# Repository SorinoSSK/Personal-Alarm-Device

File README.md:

# Introduction
This repository serves as a record and learning journey on hardware used for my capstone project. The objective of the project is to implement a small, affordable and unrestrictive IoT deviced that enables individuals to call for help in an emergency.

## PCB_Design_GSM_GPS
With the failure to find an appropriate module that carries both the functionality of GPS and GSM, I have decided to design a customised module using [SIM868](https://www.alibaba.com/product-detail/SIM868-Signal-Circuits-GSM-GPS-GNSS_1600272320629.html). SIM868 enables both GSM and GPS communication that is inline with the frequency band used in Singapore, however SIM868 is built for 2G communication and 2G communication is no longer used in Singapore. 

***Update: SIM868 is mostly no longer in production.***\
***SIM868 could not detect 3G or 4G network***

## Schematic_1
Upon searching for SIM868, I stumble across the module A9G and thus drew the schematic to be used for feasibility testing of our idea. A9G also uses GPRS protocol which still runs mostly on a [2G network](https://tinyurl.com/mwhuy22j). 

***Update: A9G could not detect 3G or 4G network***

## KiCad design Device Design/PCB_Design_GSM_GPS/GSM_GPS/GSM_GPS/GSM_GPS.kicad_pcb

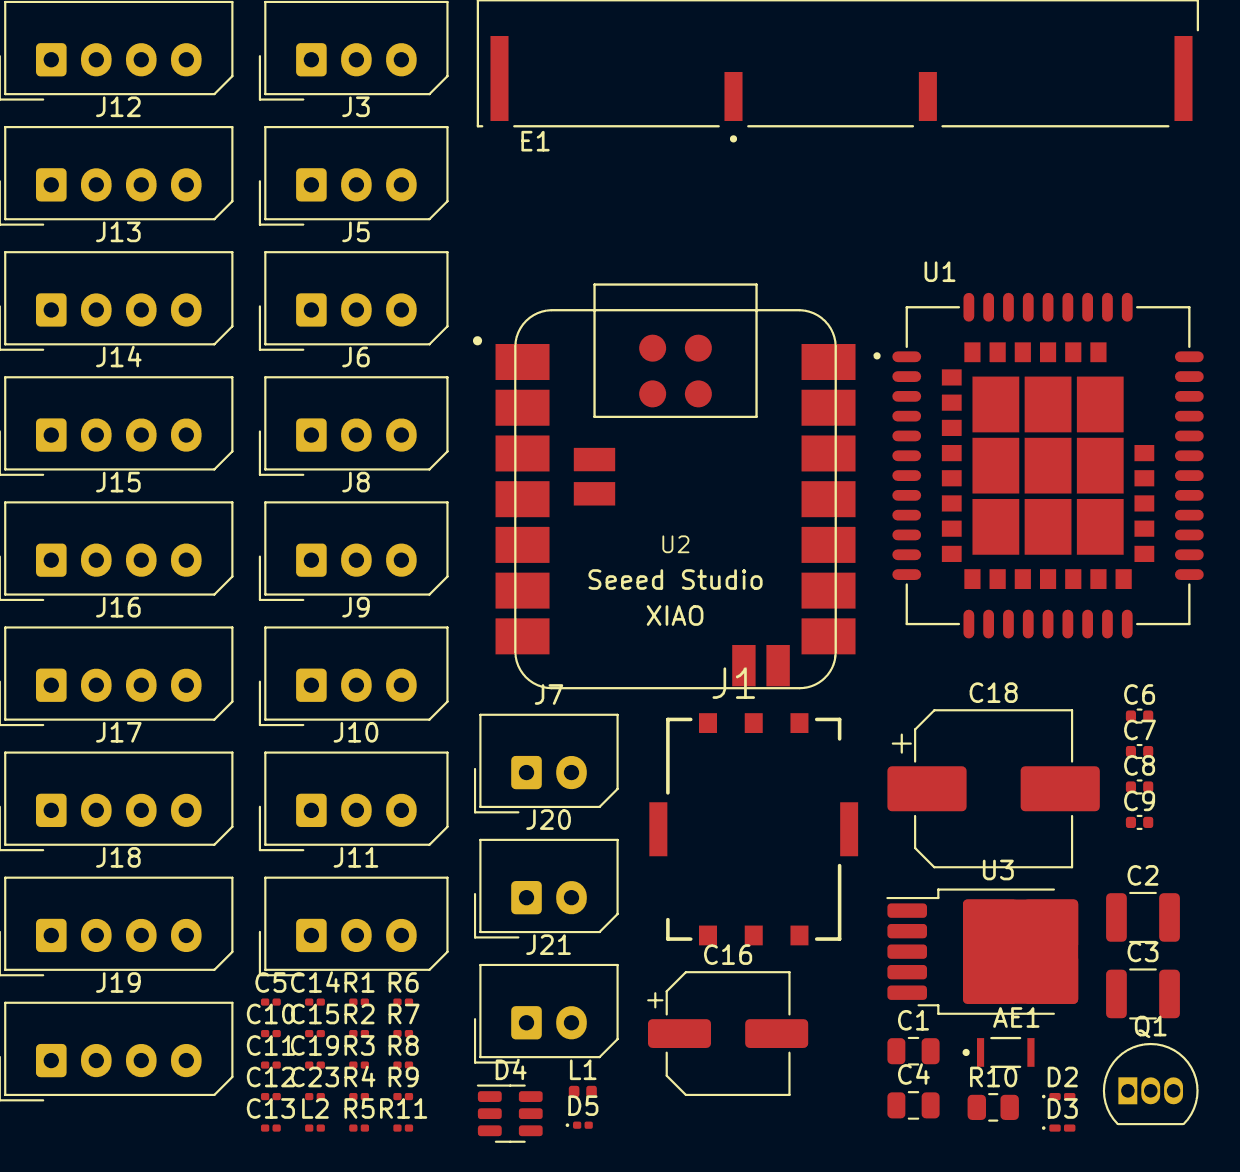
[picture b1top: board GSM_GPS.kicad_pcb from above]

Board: 2 copper layers, 63 parts (0 on the bottom side), 45 nets, no tracks yet.

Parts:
AE1: GGBLA.01.A; XCVR_GGBLA.01.A
C1, C4: 100uF; C_0805_2012Metric
C2, C3: 330uF; C_1210_3225Metric
C5: 33pF; C_0201_0603Metric
C6: 10pF; C_0402_1005Metric
C7, C8, C9: 22pF; C_0402_1005Metric
C10, C19: 0.1uF; C_0201_0603Metric
C11, C14: 0.5pF; C_0201_0603Metric
C12: 1uF; C_0201_0603Metric
C13: 0.8pF; C_0201_0603Metric
C15: 22pF; C_0201_0603Metric
C16: 100uF; CP_Elec_6.3x7.7
C18: 330uF; CP_Elec_8x10.5
C23: 2.7pF; C_0201_0603Metric
D2, D3: LED; LED_0201_0603Metric_Pad0.64x0.40mm_HandSolder
D4: ESDA6V1-5SC6; SOT-23-6
D5: 5.1V; D_0201_0603Metric
E1: YC0003AA; XCVR_YC0003AA
J1: SIM8051-6-0-14-00-X-REVD; GCT_SIM8051-6-0-14-00-X-REVD
J2, J3, J5, J6, J8, J9, J10, J11: Conn_01x03_Pin; Molex_SPOX_5267-03A_1x03_P2.50mm_Vertical
J4, J12, J13, J14, J15, J16, J17, J18, J19: Conn_01x04_Pin; Molex_SPOX_5267-04A_1x04_P2.50mm_Vertical
J7, J20, J21: Conn_01x02_Pin; Molex_SPOX_5267-02A_1x02_P2.50mm_Vertical
L1: 3.3nH; L_0402_1005Metric
L2: 6.8nH; L_0201_0603Metric
Q1: 2N3904; TO-92_Inline
R1, R2, R3: 22; R_0201_0603Metric
R4: 100k; R_0201_0603Metric
R5, R6, R7, R8: 4.7k; R_0201_0603Metric
R9: 10k; R_0201_0603Metric
R10: 43k; R_0805_2012Metric
R11: 470k; R_0201_0603Metric
U1: SIM868; XCVR_SIM868
U2: SeeeduinoXIAO nRF52840 Sense; XIAO-nRF52840-Sense-14P-2.54-21X17.8MM
U3: MIC29302AWD; TO-252-5_TabPin3

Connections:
BATTERY_IN: C12.1, C16.1, J20.1, U3.1 (EN), U3.2 (VIN)
GPIO0: J15.1, U2.1 (PA02_A0_D0)
GPIO1: J4.3, J15.2, U1.57 (GPIO1), U2.2 (PA4_A1_D1)
GPIO2: J15.3, U2.3 (PA10_A2_D2)
GPIO3: J15.4, U2.4 (PA11_A3_D3)
GPS_ANT: C23.2, U1.68 (GPS_ANT)
GPS_EN: R9.2, U1.59 (GNSS_EN)
GPS_EN_GPIO1: J21.1, R9.1
GPS_RX: J4.1, U1.23 (UART2_RXD), U1.62 (GPS_RXD)
GPS_TX: J4.2, U1.22 (UART2_TXD), U1.61 (GPS_TXD)
GSM_ANT: L1.2, U1.32 (GSM_ANT)
unnamed: C14.1, C15.1
unnamed: AE1.1 (RF_Feed), C13.1, C14.2, C23.1
unnamed: C11.1, E1.1, L1.1
unnamed: D2.2 (A), U1.41 (NETLIGHT)
unnamed: D2.1 (K), R7.1
unnamed: D3.2 (A), U1.42 (STATUS)
unnamed: D3.1 (K), R8.1
unnamed: C10.1, D4.3 (IO2), J1.C1 (VCC), U1.18 (SIM1_VDD)
unnamed: C9.1, D4.4 (IO3), J1.C7 (I/O), R1.1
unnamed: C8.1, D4.5 (IO4), J1.C3 (CLK), R2.1
unnamed: C7.1, D4.6 (IO5), J1.C2 (RST), R3.1
unnamed: E1.2, L2.1
unnamed: Q1.2 (B), R5.2, R6.1
unnamed: R2.2, U1.16 (SIM1_CLK)
unnamed: R1.2, U1.15 (SIM1_DATA)
unnamed: R3.2, U1.17 (SIM1_RST)
unnamed: R4.2, R10.1, U3.5 (ADJ)
POWER_BTN: J2.2, R5.1
POWER_PIN: J7.1, Q1.3 (C), U1.39 (PWRKEY)
SCL: J5.2, J6.2, U1.65 (SCL)
SDA: J5.1, J6.1, U1.64 (SDA)
SIM868_Vin: C1.1, C2.1, C3.1, C4.1, C5.1, C6.1, C18.1, C19.1, D5.1 (K), J19.1, J19.2, J19.3, J19.4, R4.1, R11.1, U1.28 (VRTC), U1.34 (GPS_VBAT), U1.35 (VBAT), U3.4 (VOUT)
UART1_RX: J3.1, U1.2 (UART1_RXD)
UART1_TX: J3.2, U1.1 (UART1_TXD)
XIAO_3.3V: J17.1, J17.2, J17.3, J17.4, U2.12 (3V3)
XIAO_5V: J18.1, J18.2, J18.3, J18.4, U2.14 (5V)
XIAO_GND: AE1.2 (gnd), C1.2, C2.2, C3.2, C4.2, C5.2, C6.2, C7.2, C8.2, C9.2, C10.2, C11.2, C12.2, C13.2, C15.2, C16.2, C18.2, C19.2, D4.2 (GND), D5.2 (A), J1.C5 (GND), J2.3, J3.3, J4.4, J5.3, J6.3, J7.2, J8.3, J9.3, J10.3, J11.3, J12.4, J13.4, J14.4, J16.1, J16.2, J16.3, J16.4, J20.2, J21.2, L2.2, Q1.1 (E), R6.2, R7.2, R8.2, R10.2, R11.2, U1.8 (GND), U1.13 (GND), U1.19 (GND), U1.21 (GND), U1.27 (GND), U1.30 (GND), U1.31 (GND), U1.33 (GND), U1.36 (GND), U1.37 (GND), U1.45 (GND), U1.63 (GND), U1.66 (GND), U1.67 (GND), U1.69 (GND), U1.70 (GND), U1.71 (GND), U1.72 (GND), U1.73 (GND), U1.74 (GND), U1.75 (GND), U1.76 (GND), U1.77 (GND), U2.13 (GND), U3.3 (GND)
XIAO_I2C_SCL: J9.2, J10.2, J11.2, U2.6 (PA9_A5_D5_SCL)
XIAO_I2C_SDA: J9.1, J10.1, J11.1, U2.5 (PA8_A4_D4_SDA)
XIAO_SPI_MISO: J12.2, J13.2, J14.2, U2.10 (PA5_A9_D9_MISO)
XIAO_SPI_MOSI: J12.1, J13.1, J14.1, U2.11 (PA6_A10_D10_MOSI)
XIAO_SPI_SCK: J12.3, J13.3, J14.3, U2.9 (PA7_A8_D8_SCK)
XIAO_UART_RX: J8.2, U2.8 (PB09_A7_D7_RX)
XIAO_UART_TX: J8.1, U2.7 (PB08_A6_D6_TX)

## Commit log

2023-11-09 Initialise schematic
2023-11-12 Update full schematic
2023-11-13 Update new schematic
2023-12-01 Upload Test Code
2024-01-02 Update Repo with Main Hardware code and IMU Data collection code
2024-01-23 Added Particle Test Code
2024-01-24 Update Cellular Code
2024-01-26 Upload 2nd version
2024-01-28 Added Bluetooth authentication and MIC
2024-01-29 Modified MICcode
2024-01-29 Modified Mic code to stream
2024-01-29 Update Contact Name change and bluetooth feedback
2024-01-30 Testing Microphone ISR 1
2024-02-02 Added button with debouncing and fix MIC streaming
2024-02-03 Clean up code
2024-02-06 Update IMUlogging with run time
2024-02-06 Add Battery Reading
2024-02-07 Update battery offset and IMU Test
2024-02-07 add kalman filter and LED status
2024-02-15 add system admin and mean filter
2024-02-15 Added device reset, sysadmin reset and battery limit unbound view
2024-02-16 Add falling training script
2024-02-21 Change battery's lower bound voltage
2024-02-22 Value Findings
2024-02-22 Update some findings
2024-02-23 Update some IMU findings
2024-02-28 Update data analysis
2024-02-28 Update Arduino Code with treshold for fall detection
2024-02-28 Added Logistic Regression
2024-02-29 abandon
2024-03-01 Update logistic regression
2024-03-06 Update switched code with latch debounce
2024-03-07 Update Buzzer and LED blink
2024-03-12 Update program to run memory first
2024-03-15 Add BLE message when disabling emergency trigger
2024-03-21 Add Battery Low and Charging Indicator, Add Active Buzzer Beep
2024-03-23 Include User Token
2024-03-26 Include RSSI distance measurement
2024-03-29 Update program with bootup indication
2024-03-29 Add Logistic regression training
2024-03-29 remove images
2024-03-29 restructure file
2024-03-31 Update Data
